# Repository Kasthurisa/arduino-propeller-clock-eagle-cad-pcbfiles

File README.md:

# arduino-propeller-clock-eagle-cad-pcbfiles
here are the eagle cad pcb files for the arduino based propeller clock

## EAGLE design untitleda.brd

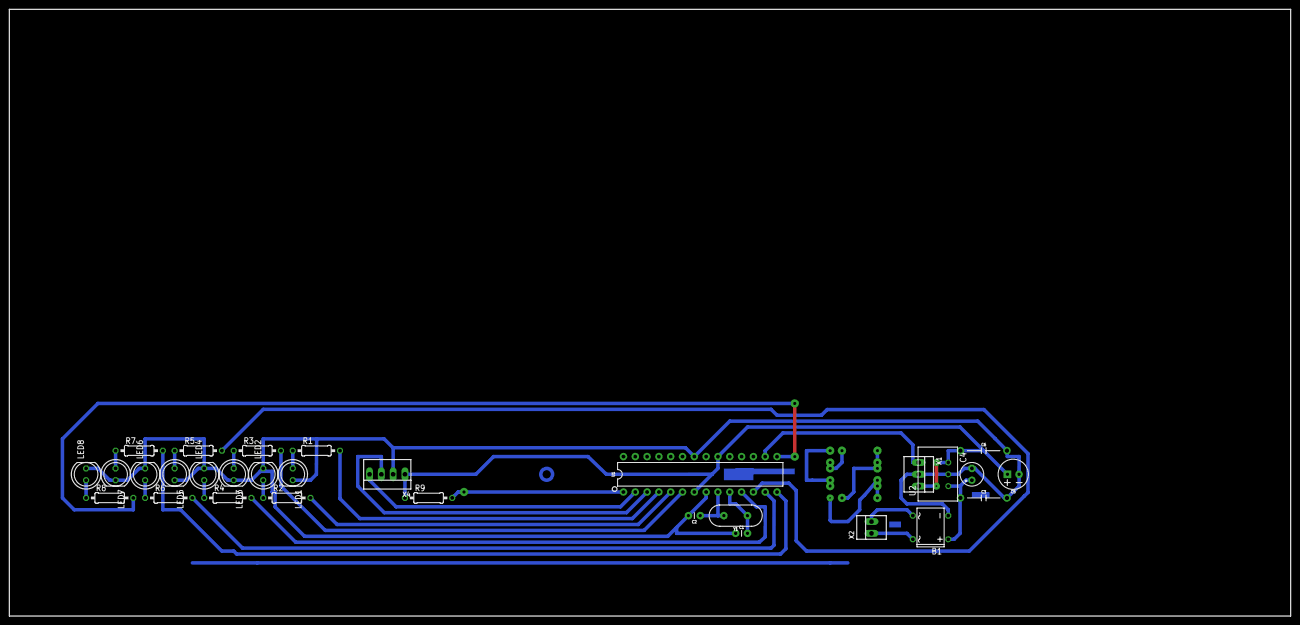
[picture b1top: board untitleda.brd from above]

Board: 2 copper layers, 275.6 x 130.5 mm, 30 parts (0 on the bottom side), 27 nets.

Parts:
B1: DBDB107G; DB
C1, C2: 22pF; CAP-PTH-2.54
C3, C6: 10nF; CAP-PTH-10MM
C4: E2,5-5
C5: 100uF; CPOL-RADIAL-2.5MM-6.5MM
LED1, LED2, LED3, LED4, LED5, LED6, LED7, LED8: LED5MM
R1, R2, R3, R4, R5, R6, R7, R8, R9: 0207/10
U1: 328P; DIP28
U2: R-78E5.0-1.0; DC-DC_CONVERTER_78XX
X1: 22-23-2031
X2: 22-23-2021
X4: 22-23-2041
Y1: 16MHz; HC49US

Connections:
2: R1.2, U1.4
3: R2.2, U1.5
4: R3.2, U1.6
5: R4.2, U1.11
5V: C5.1, C6.1, R9.1, U1.7, U1.20, U2.VOUT, X1.3, X4.1
6: R5.2, U1.12
7: R6.2, U1.13
8: R7.2, U1.14
9: R8.2, U1.15
unnamed: LED1.A, R1.1
unnamed: LED2.A, R2.1
unnamed: LED3.A, R3.1
unnamed: LED4.A, R4.1
unnamed: LED5.A, R5.1
unnamed: LED6.A, R6.1
unnamed: LED7.A, R7.1
unnamed: LED8.A, R8.1
unnamed: C1.2, U1.10, Y1.1
unnamed: B1.+, C3.1, C4.+, U2.VIN
unnamed: B1.AC2, X2.1
unnamed: U1.2, X4.4
unnamed: U1.3, X4.3
unnamed: B1.AC1, X2.2
unnamed: R9.2, U1.1
unnamed: B1.-, C1.1, C2.2, C3.2, C4.-, C5.2, C6.2, LED1.K, LED2.K, LED3.K, LED4.K, LED5.K, LED6.K, LED7.K, LED8.K, U1.8, U1.22, U2.GND, X1.2, X4.2
unnamed: U1.16, X1.1
unnamed: C2.1, U1.9, Y1.2

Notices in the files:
parts and their libraries:
SparkFun-Capacitors: Licensing: Creative Commons ShareAlike 4.0 International - https://creativecommons.org/licenses/by-sa/4.0
